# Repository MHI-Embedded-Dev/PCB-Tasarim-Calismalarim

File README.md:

# PCB-Tasarim-Calismalarim
Phil’s Lab kanalının çekmiş olduğu PCB desigm serisinde bulunan kartları kendime göre revizeler ederek yaptığım çalışmalar

KiCad STM32 + USB + Buck Converter PCB Design başlıklı videonun devre tasarımını yaptım.

STM32F405 mikrodenetleyici ile yapmış olduğum tasarımın Şematik, PCB ve 3D görüntüsü verilmiştir.

Kart Özellikleri
- 1 Adet I2C Çıkışı
- 1 Adet UART Çıkışı
- USB Micro 10MB/ps veri aktarım hızlı Çıkış
- 12 V Besleme Girişi
- Statues ve 3.3V Ledi
- Buck Converter Devresi
- SWD Programlama Çıkışları

3D GÖRÜNTÜSÜ

ŞEMATİK TASARIMI
[Şematik_PDF.pdf](https://github.com/MHI-Embedded-Dev/PCB-Tasarim-Calismalarim/files/12449016/Sematik_PDF.pdf)

PCB TASARIMI
[PCB_PDF.pdf](https://github.com/MHI-Embedded-Dev/PCB-Tasarim-Calismalarim/files/12449017/PCB_PDF.pdf)

KiCad ve Gerber dosyaları klasör içerisinde mevcuttur.

Herhangi bir sorunuz olması durumunda severek yardımcı olacağımı belirtmek isterim....

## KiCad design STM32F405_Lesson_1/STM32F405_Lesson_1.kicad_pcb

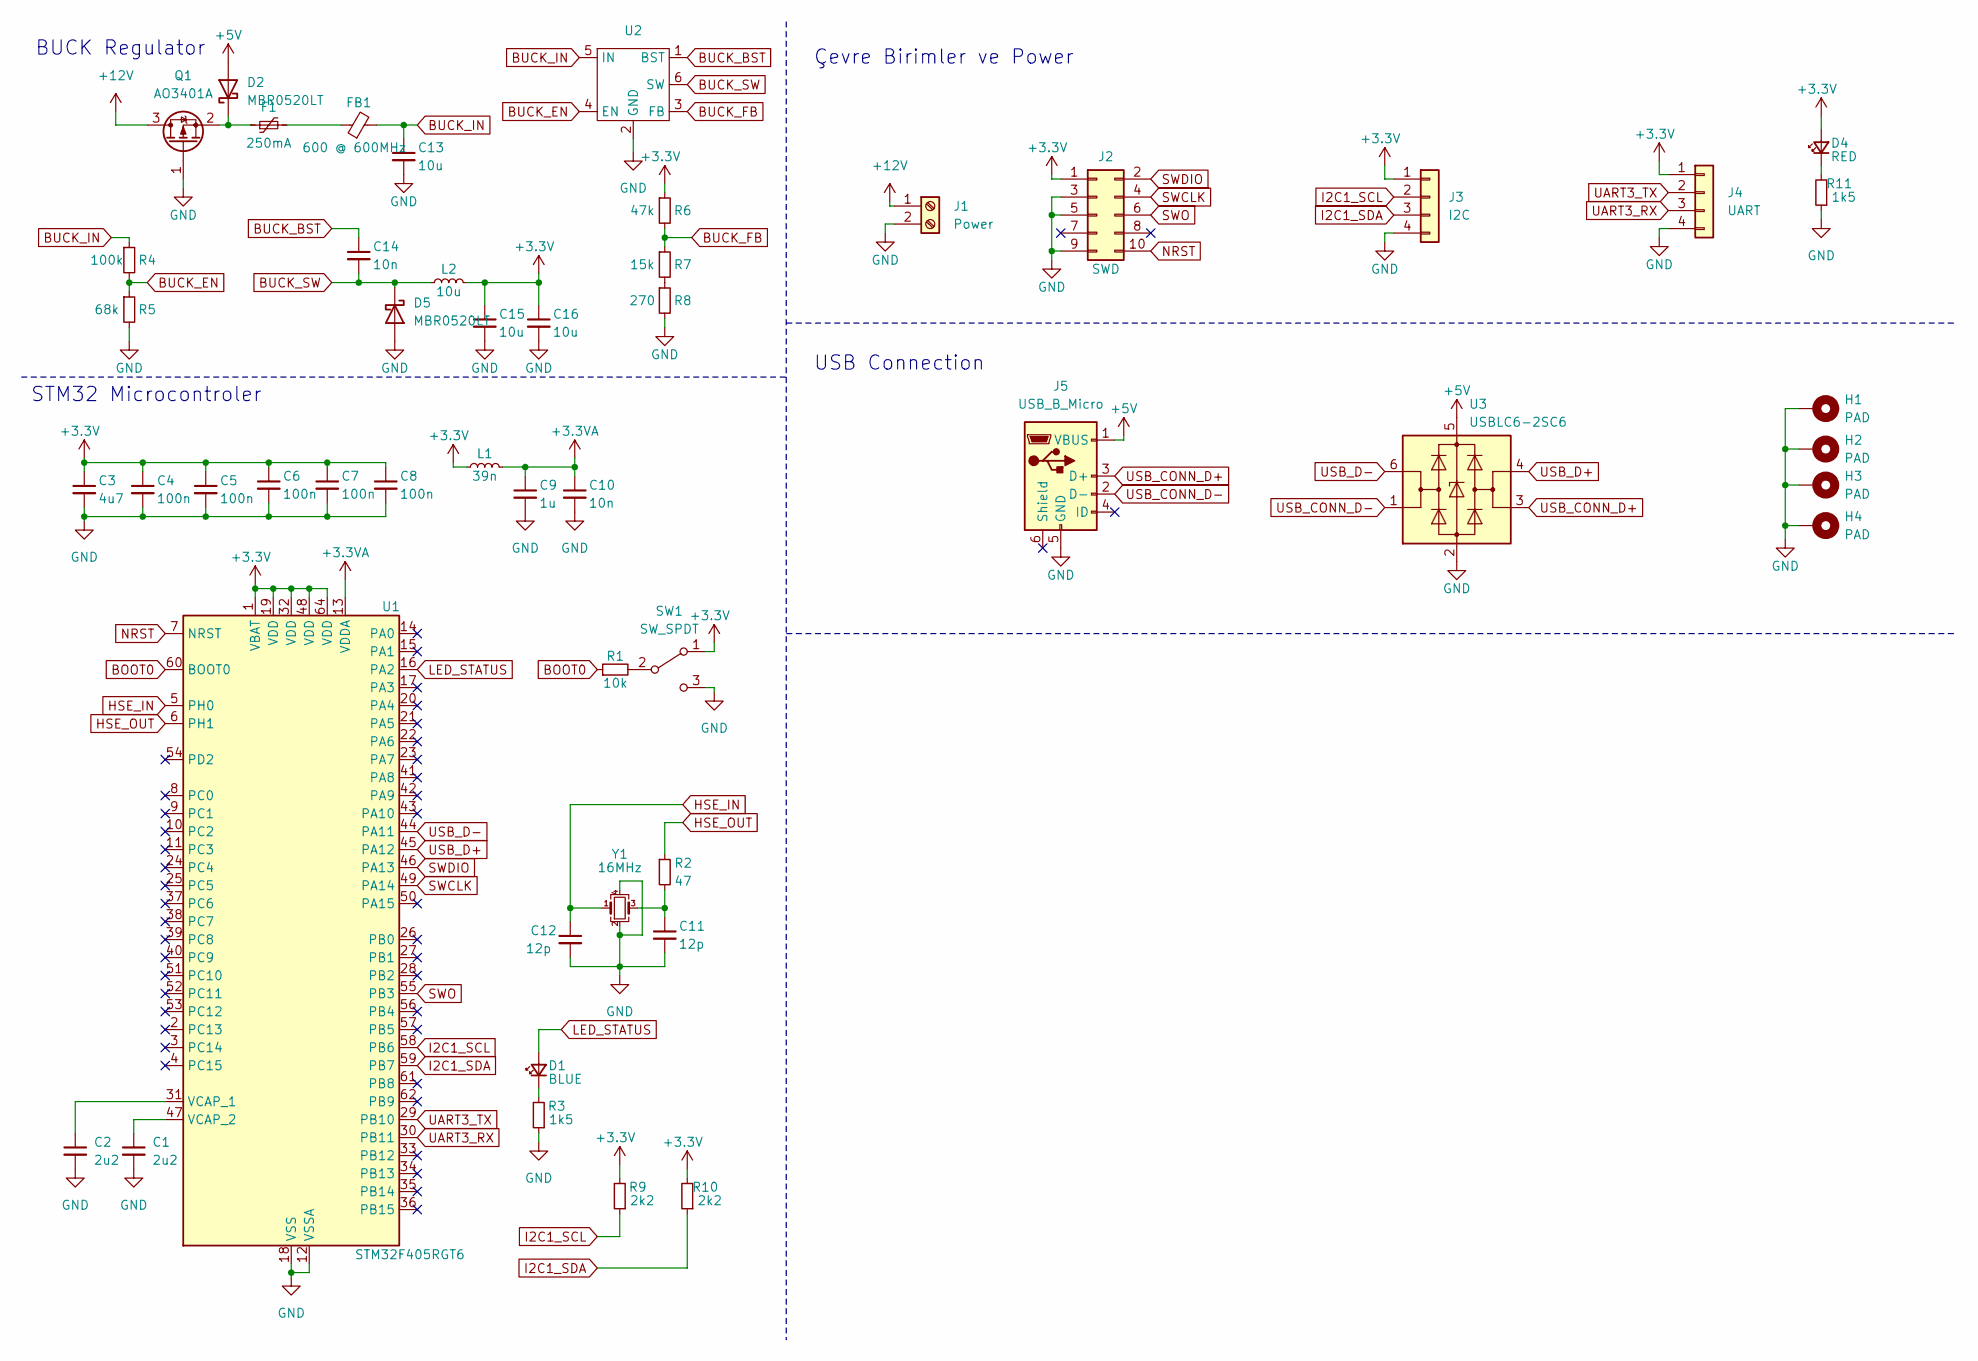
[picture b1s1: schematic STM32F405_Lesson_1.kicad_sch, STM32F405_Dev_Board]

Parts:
C1, C2: 2u2; C_0603_1608Metric
C3: 4u7; C_0603_1608Metric
C4, C5, C6, C7, C8: 100n; C_0402_1005Metric
C9: 1u; C_0402_1005Metric
C10: 10n; C_0402_1005Metric
C11, C12: 12p; C_0402_1005Metric
C13, C15, C16: 10u; C_1206_3216Metric
C14: 10n; C_0603_1608Metric
D1: BLUE; LED_0603_1608Metric
D2, D5: MBR0520LT; D_SOD-123
D4: RED; LED_0603_1608Metric
F1: 250mA; Fuse_1206_3216Metric
FB1: 600 @ 600MHz; L_0805_2012Metric
H1, H2, H3, H4: PAD; MountingHole_4.3mm_M4_Pad_Via
J1: Power; PhoenixContact_MCV_1,5_2-G-3.5_1x02_P3.50mm_Vertical
J2: SWD; PinSocket_2x05_P1.27mm_Vertical_SMD
J3: I2C; Molex_PicoBlade_53261-0471_1x04-1MP_P1.25mm_Horizontal
J4: UART; Molex_PicoBlade_53261-0471_1x04-1MP_P1.25mm_Horizontal
J5: USB_B_Micro; USB_Micro-B_Amphenol_10118193-0001LF_Horizontal
L1: 39n; L_0402_1005Metric
L2: 10u; L_Sunlord_MWSA0402S
Q1: AO3401A; SOT-23
R1: 10k; R_0402_1005Metric
R2: 47; R_0402_1005Metric
R3, R11: 1k5; R_0603_1608Metric
R4: 100k; R_0603_1608Metric
R5: 68k; R_0603_1608Metric
R6: 47k; R_0603_1608Metric
R7: 15k; R_0603_1608Metric
R8: 270; R_0603_1608Metric
R9, R10: 2k2; R_0402_1005Metric
SW1: SW_SPDT; SW_SPDT_PCM12
U1: STM32F405RGT6; LQFP-64_10x10mm_P0.5mm
U2: SOT-23-6
U3: USBLC6-2SC6; SOT-23-6
Y1: 16MHz; Crystal_SMD_3225-4Pin_3.2x2.5mm

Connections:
+3.3V: C3.1, C4.1, C5.1, C6.1, C7.1, C8.1, C15.1, C16.1, D4.2 (A), J2.1, J3.1, J4.1, L1.1, L2.2, R6.1, R9.2, R10.2, SW1.1 (A), U1.1 (VBAT), U1.19 (VDD), U1.32 (VDD), U1.48 (VDD), U1.64 (VDD)
+3.3VA: C9.1, C10.1, L1.2, U1.13 (VDDA)
+5V: D2.2 (A), J5.1 (VBUS), U3.5 (VBUS)
+12V: J1.1, Q1.3 (D)
BOOT0: R1.1, U1.60 (BOOT0)
BUCK_BST: C14.1, U2.1 (BST)
BUCK_EN: R4.2, R5.1, U2.4 (EN)
BUCK_FB: R6.2, R7.1, U2.3 (FB)
BUCK_IN: C13.1, FB1.2, R4.1, U2.5 (IN)
BUCK_SW: C14.2, D5.1 (K), L2.1, U2.6 (SW)
GND: C1.2, C2.2, C3.2, C4.2, C5.2, C6.2, C7.2, C8.2, C9.2, C10.2, C11.2, C12.2, C13.2, C15.2, C16.2, D5.2 (A), H1.1, H2.1, H3.1, H4.1, J1.2, J2.3, J2.5, J2.9, J3.4, J4.4, J5.5 (GND), Q1.1 (G), R3.1, R5.2, R8.2, R11.1, SW1.3 (C), U1.12 (VSSA), U1.18 (VSS), U1.63 (VSS), U2.2 (GND), U3.2 (GND), Y1.2, Y1.4
HSE_IN: C12.1, U1.5 (PH0), Y1.1
HSE_OUT: R2.1, U1.6 (PH1)
I2C1_SCL: J3.2, R9.1, U1.58 (PB6)
I2C1_SDA: J3.3, R10.1, U1.59 (PB7)
LED_STATUS: D1.2 (A), U1.16 (PA2)
NRST: J2.10, U1.7 (NRST)
unnamed: C11.1, R2.2, Y1.3
unnamed: D1.1 (K), R3.2
unnamed: D2.1 (K), F1.1, Q1.2 (S)
unnamed: D4.1 (K), R11.2
unnamed: F1.2, FB1.1
unnamed: R7.2, R8.1
unnamed: R1.2, SW1.2 (B)
unnamed: C2.1, U1.31 (VCAP_1)
unnamed: C1.1, U1.47 (VCAP_2)
SWCLK: J2.4, U1.49 (PA14)
SWDIO: J2.2, U1.46 (PA13)
SWO: J2.6, U1.55 (PB3)
UART3_RX: J4.3, U1.30 (PB11)
UART3_TX: J4.2, U1.29 (PB10)
USB_CONN_D+: J5.3 (D+), U3.3 (I/O2)
USB_CONN_D-: J5.2 (D-), U3.1 (I/O1)
USB_D+: U1.45 (PA12), U3.4 (I/O2)
USB_D-: U1.44 (PA11), U3.6 (I/O1)

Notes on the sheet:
USB Connection
STM32 Microcontroler
Çevre Birimler ve Power
BUCK Regulator

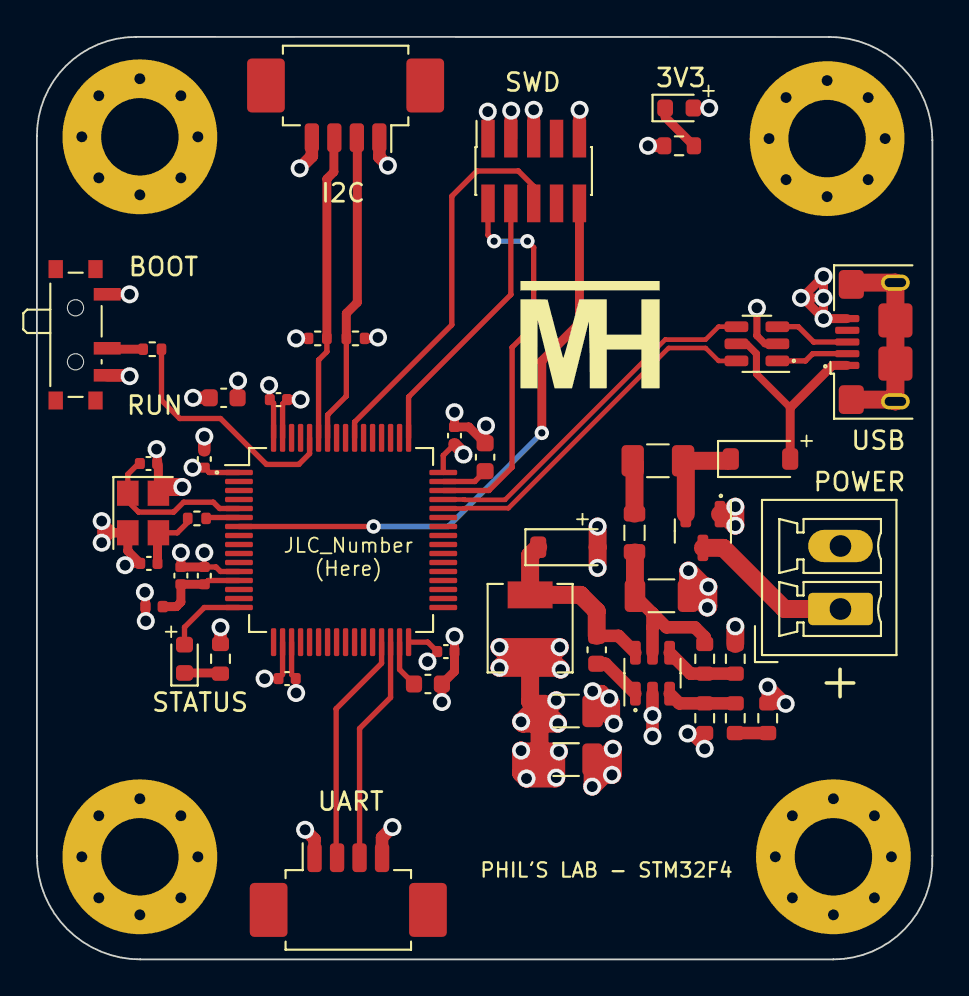
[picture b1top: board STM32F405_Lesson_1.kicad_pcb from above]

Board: 4 copper layers, 49.8 x 51.2 mm, 50 parts (0 on the bottom side), 35 nets.

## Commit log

2023-08-27 KiCad STM32 + USB + Buck Converter PCB Design
    Phil's Lab kanalının çekmiş olduğu PCB Design adlı oynatma listesinde tasarladığı ilk devre kartı kendi revizelerimi yaparak burada yayımladım
